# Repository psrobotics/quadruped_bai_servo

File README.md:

# Quadruped_bai_servo v1

A low cost 12DOF quadruped, actuated by hobby servos. Notice that this is an early version developed back in 2019. If you're looking for a high performance desktop quad, check out the ongoing [Quadruped bai tiny](https://github.com/psrobotics/Quadruped_bai_tiny)

This repository contains the models, BOM, electronic, simulate, as well as the source code of the project.

## Videos

[Balancing](https://www.youtube.com/watch?v=fsc0w1NeIVk)

[Walking](https://youtu.be/FCRvykWv6ok)

## Hardware

Required parts are listed below. For all printed parts, the recommended printing infill is 70%. Set up proper printing direction and support based on your printer type.

| Part Name                                                   | Quantity | Link                                                         | Info                |
| ----------------------------------------------------------- | -------- | ------------------------------------------------------------ | ------------------- |
| leg_tip                                                     | 2        | [STL file](hardware/stl)                                     | Printed part        |
| leg_tip_MIR                                                 | 2        | /                                                            | /                   |
| leg_2                                                       | 2        | /                                                            | /                   |
| leg_2_MIR                                                   | 2        | /                                                            | /                   |
| leg_link_1                                                  | 2        | /                                                            | /                   |
| leg_link_1_MIR                                              | 2        | /                                                            | /                   |
| leg_link-1                                                  | 2        | /                                                            | /                   |
| leg_link-1_MIR                                              | 2        | /                                                            | /                   |
| leg_1                                                       | 2        | /                                                            | /                   |
| leg_1_MIR                                                   | 2        | /                                                            | /                   |
| leg_1_2                                                     | 2        | /                                                            | /                   |
| leg_1_2_MIR                                                 | 2        | /                                                            | /                   |
| servo_holder_1                                              | 2        | /                                                            | /                   |
| servo_holder_1_MIR                                          | 2        | /                                                            | /                   |
| hip_joint_holder_1                                          | 2        | /                                                            | /                   |
| hip_joint_holder_1_MIR                                      | 2        | /                                                            | /                   |
| hip_holder_2                                                | 2        | /                                                            | /                   |
| hip_holder_2_MIR                                            | 2        | /                                                            | /                   |
| joint_ab_holder                                             | 2        | /                                                            | /                   |
| body_bridge                                                 | 2        | /                                                            | /                   |
| body_frame_2                                                | 1        | /                                                            | /                   |
| body_frame_1                                                | 1        | /                                                            | /                   |
| pcb_holder                                                  | 2        | /                                                            | /                   |
| M3*8                                                        | ~20      | /                                                            | Screw               |
| M3*12                                                       | ~30      | /                                                            | /                   |
| M3*16                                                       | ~20      | /                                                            | /                   |
| M2*8                                                        | ~50      | /                                                            | /                   |
| M2*15                                                       | ~50      | /                                                            | /                   |
| M2*20                                                       | ~20      | /                                                            | /                   |
| M2*26                                                       | ~20      | /                                                            | /                   |
| SF-1 0305 Self Lubricating Composite Bearing Bushing Sleeve | ~25      | [ebay](https://www.ebay.com/itm/141882850401?_trkparms=amclksrc%3DITM%26aid%3D1110006%26algo%3DHOMESPLICE.SIM%26ao%3D1%26asc%3D20200818143230%26meid%3Df2f23010710f47e39153549f7afe6b5b%26pid%3D101224%26rk%3D2%26rkt%3D5%26sd%3D141882852158%26itm%3D141882850401%26pmt%3D0%26noa%3D1%26pg%3D2047675%26algv%3DDefaultOrganicWeb%26brand%3DUnbranded&_trksid=p2047675.c101224.m-1) | For rotation joints |
| EMAX ES08A II Servo                                         | 12       | [EMAX](https://emaxmodel.com/products/emax-es08a-ii-mini-plastic-gear-analog-servo-1-8kg-sec-for-rc-models-robot) | Actuator            |

After printing your parts, insert the bearing at all 5mm holes locates around rotations joints. Then fasten  parts with M3 screws. Remember to check the rotation friction, make sure all joints can rotates freely with the servo installed. 

### Servo selection

The performance of actuators is of fundamental importance for legged robots. Even when we're building a small one. Ideal actuators for this design should be highly back-drivable, have high power density, and be torque-controllable. However, most off-the-shelf servos have nothing to do with these features. There are some high voltage brushless servos (with magnetic encoders for feedback) with relatively good performance, but they're extremely costive at this size. If you have enough budget, why not build a brushless one? Considering that you'll need 12 servos for the assembly, my suggestion is just to go for the budget choice. The EMAX ES08A (metal gear version) works fine for my build. The nylon gear version is also acceptable, but they can easily be damaged under impact.

### Body assembly

The robot consists 4 legs and a body frame. Assembly 2 legs first.

Assembly another 2 mirrored legs. Then link all legs to the body frame.

### Feet Sensor (optional)

Additional feet sensors can detect whether foot have touched the ground. This can be helpful when changing the state machine from 'swing state' to 'stance state'. The foot of Quadruped bai servo is switchable. If you decided to add feet sensors, some additional configurations are needed for the firmware (would be detailly explained later). 

Feet sensors are built around micro switches,  which detect impact from specific directions. As for the result, this design didn't work that well. A good feet sensor solution should be able to detect impacts from all directions, with low latency and clear output. [Open Dynamic Robot Initiative](https://open-dynamic-robot-initiative.github.io/) has presented an elegant solution with infrared sensor. Take that as a reference, the ongoing Quadruped bai tiny will come with better feet sensors. Assembly the feet sensor as this pic shown. (Remember to print mirrored parts for right-side legs)

Only 3 printed parts are needed to assembly the feet sensor, check [STL file](hardware/stl/feet_sensor) here.

In order to increase the friction between feet and ground, additional high-friction coating is vital. I used some glued silicone sheet on the feet tip. You can also design your feet tip and print it with high-friction material.

### Servo Calibration

Most servos have a limited motion range,  make sure the servo's motion range covers leg linkage's joint limit shown in the following pics.  Also, pre-calibrate in this step by applying an initial PWM signal to servos before installing (eg. 0°). This enables all servos to have the same PWM-joint angle mapping. You can then fine-tuning them in the firmware.

## Electronic

The controller board assembly includes servo controller, IMU, and dc-dc converter module. With an additional serial port, you can connect robot to a wireless or Bluetooth module that enables wireless control. Built around ATmega328P, the microcontroller's performance, IO is just not enough for such application. I encourage you take this schematic as a reference and switch to a high performance 32-bit microcontroller (something like STM32H7, ESP32). If you're more comfortable with AVR Arduino boards, use this design directly and it'll work.

[PCBs](electronic/) are designed with [EAGLE](https://www.autodesk.com/products/eagle/free-download). Exported Gerber file is uploaded too. If you don't want to order the PCB, you can also make it using off-the-shelf components (Arduino nano, MPU 6050, dc-dc converter, etc).

### Controller board pin assignment

Use ICSP to upload firmware and debug with the external serial port. The hardware IIC pins(A4,A5) are occupied by IMU (MPU6050 is also an 'old chip', you can replace with something like BNO080). 

### DC-DC converter

Integrated boost converter to power servos. Pre-configured output voltage is 5.5V, you can change by [replacing](https://www.ti.com/lit/ds/symlink/tps61088.pdf?ts=1644121246192#:~:text=The%20TPS61088%20is%20a%20high,size%20solution%20in%20portable%20systems.&text=The%20device%20has%2010%2DA,voltage%20up%20to%2012.6%20V.) the feedback resistor. Plug this module to the DC-DC slot on controller board.

### Battery

Single-cell lithium batteries with high current output capability(>10A) are preferred. This project uses 18650, 18350 batteries. The [battery shelf](hardware/step) can be printed and mounted under the robot frame.

## Simulate

Simplified model in [v-rep](https://www.coppeliarobotics.com/). You can use remote API to develop your simulation.

### Coordinate system in the simulation

TODO, write this docu when I'm free.

## Firmware

A simplified controller is implemented to generate trot pattern for walking. Here, I applied a state machine to easily synchronize a set of open foot trajectories (with feet sensor). The IMU unit is used to adjust body roll&pitch during the stance phase. Notice that this robot is only controlled on the kinematic level, don't expect it to resist external impacts during walking process.

## License

Under BSD-3-Clause license, COME WITH NO WARRANTIES, BUILD AT YOUR RISK.

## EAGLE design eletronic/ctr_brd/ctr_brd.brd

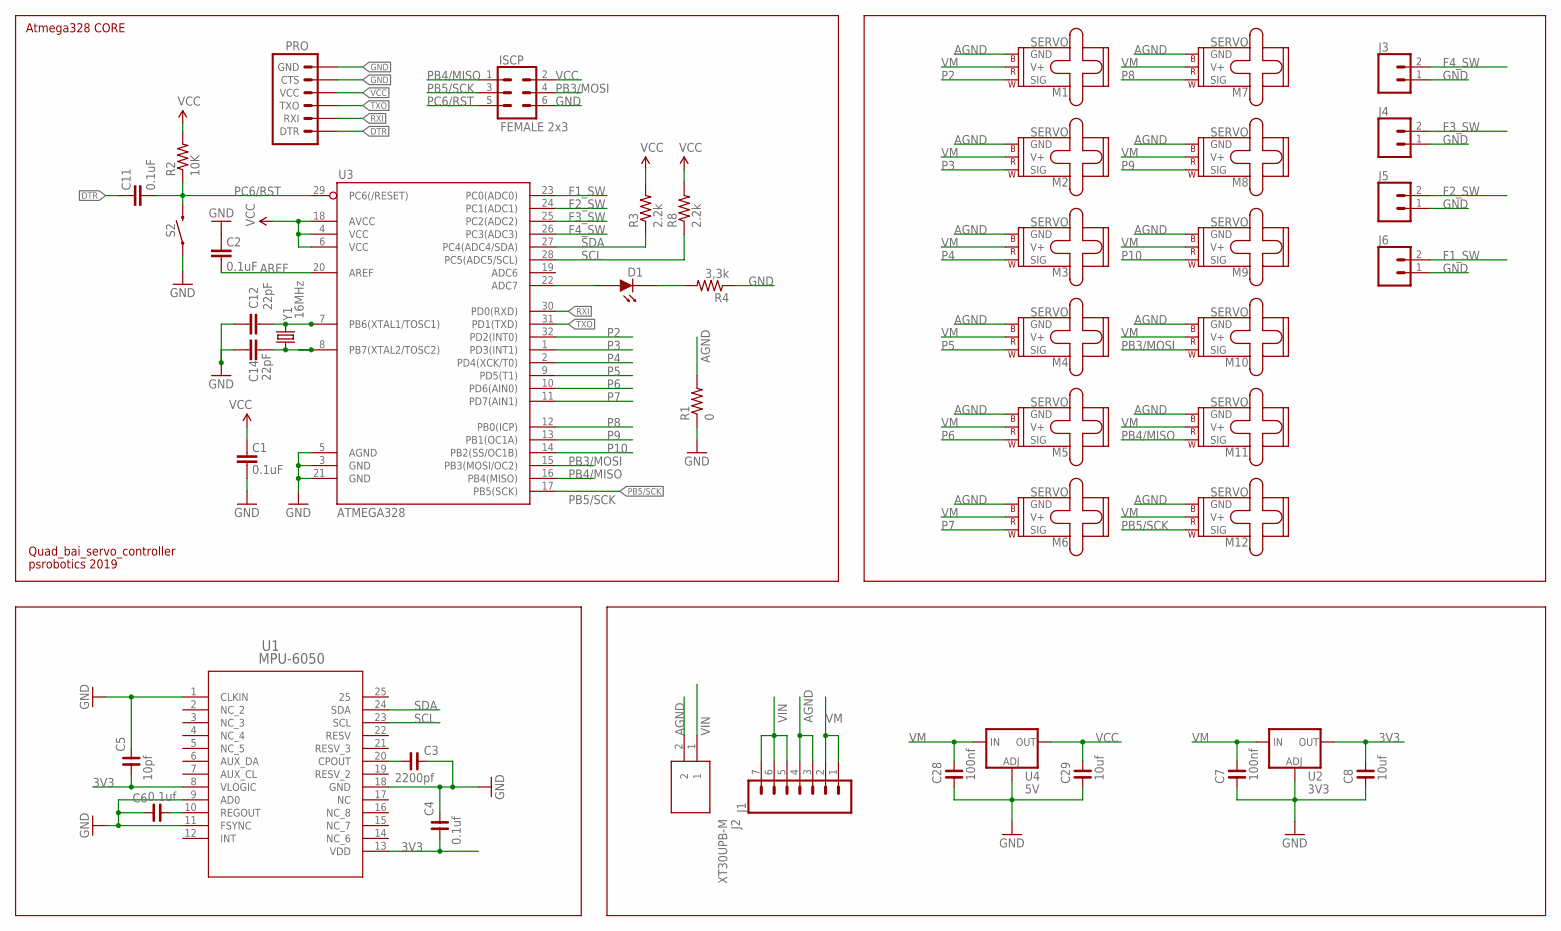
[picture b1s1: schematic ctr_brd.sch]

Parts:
C1, C2, C11: 0.1uF; 0603-CAP
C3: 2200pf; C0603
C4, C6: 0.1uf; C0603
C5: 10pf; C0603
C7, C28: 100nf; C0603
C8, C29: 10uf; C0603
C12, C14: 22pF; 0603
D1: LEDB; 0603P
ISCP: FEMALE 2x3; 2X3
J1: CONN_07LONGPADS; 1X07_LONGPADS
J2: XT30UPB-M; SHDR2W160P0X500_1X2_1020X520X1
J3, J4, J5, J6: CONN_02LOCK; 1X02_LOCK
M1, M2, M3, M4, M5, M6, M7, M8, M9, M10, M11, M12: SERVO; 1X03
PRO: FTDI Basic; 1X06
R1: 0; 0603-RES
R2: 10K; 0603-RES
R3, R8: 2.2k; 0603-RES
R4: 3,3k; 0603-RES
S2: MOMENTARY-SWITCH-SPST-SMD-6.0X3.5MM; TACTILE_SWITCH_SMD_6.0X3.5MM
U1: MPU-6050; QFN24_4X4X0P9_IVS
U2: 3V3; SOT223
U3: ATMEGA328; TQFP32-08
U4: 5V; SOT223
Y1: 16MHz; CRYSTAL-SMD-5X3.2-4PAD

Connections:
3V3: C4.1, C5.1, C8.2, U1.8 (VLOGIC), U1.13 (VDD), U2.2 (OUT), U2.4 (OUT)
AGND: J1.3, J1.4, J2.2, M1.3 (GND), M2.3 (GND), M3.3 (GND), M4.3 (GND), M5.3 (GND), M6.3 (GND), M7.3 (GND), M8.3 (GND), M9.3 (GND), M10.3 (GND), M11.3 (GND), M12.3 (GND), R1.2
AREF: C2.1, U3.20 (AREF)
DTR: C11.2, PRO.1 (DTR)
F1_SW: J6.2, U3.23 (PC0(ADC0))
F2_SW: J5.2, U3.24 (PC1(ADC1))
F3_SW: J4.2, U3.25 (PC2(ADC2))
F4_SW: J3.2, U3.26 (PC3(ADC3))
GND: C1.1, C2.2, C3.2, C4.2, C5.2, C6.2, C7.1, C8.1, C12.1, C14.1, C28.1, C29.1, ISCP.6, J3.1, J4.1, J5.1, J6.1, PRO.5 (CTS), PRO.6 (GND), R1.1, R4.1, S2.1, U1.1 (CLKIN), U1.9 (AD0), U1.11 (FSYNC), U1.18 (GND), U2.1 (ADJ), U3.3 (GND), U3.5 (AGND), U3.21 (GND), U4.1 (ADJ)
unnamed: C14.2, U3.8 (PB7(XTAL2/TOSC2)), Y1.1
unnamed: C12.2, U3.7 (PB6(XTAL1/TOSC1)), Y1.3 (2)
unnamed: C3.1, U1.20 (CPOUT)
unnamed: C6.1, U1.10 (REGOUT)
unnamed: D1.1 (D_IN), U3.22 (ADC7)
unnamed: D1.2 (D_OUT), R4.2
P2: M1.1 (SIG), U3.32 (PD2(INT0))
P3: M2.1 (SIG), U3.1 (PD3(INT1))
P4: M3.1 (SIG), U3.2 (PD4(XCK/T0))
P5: M4.1 (SIG), U3.9 (PD5(T1))
P6: M5.1 (SIG), U3.10 (PD6(AIN0))
P7: M6.1 (SIG), U3.11 (PD7(AIN1))
P8: M7.1 (SIG), U3.12 (PB0(ICP))
P9: M8.1 (SIG), U3.13 (PB1(OC1A))
P10: M9.1 (SIG), U3.14 (PB2(SS/OC1B))
PB3/MOSI: ISCP.4, M10.1 (SIG), U3.15 (PB3(MOSI/OC2))
PB4/MISO: ISCP.1, M11.1 (SIG), U3.16 (PB4(MISO))
PB5/SCK: ISCP.3, M12.1 (SIG), U3.17 (PB5(SCK))
PC6/RST: C11.1, ISCP.5, R2.1, S2.2, U3.29 (PC6(/RESET))
RXI: PRO.2 (RXI), U3.30 (PD0(RXD))
SCL: R8.1, U1.23 (SCL), U3.28 (PC5(ADC5/SCL))
SDA: R3.1, U1.24 (SDA), U3.27 (PC4(ADC4/SDA))
TXO: PRO.3 (TXO), U3.31 (PD1(TXD))
VCC: C1.2, C29.2, ISCP.2, PRO.4 (VCC), R2.2, R3.2, R8.2, U3.4 (VCC), U3.6 (VCC), U3.18 (AVCC), U4.2 (OUT), U4.4 (OUT)
VIN: J1.5, J1.6, J1.7, J2.1
VM: C7.2, C28.2, J1.1, J1.2, M1.2 (V+), M2.2 (V+), M3.2 (V+), M4.2 (V+), M5.2 (V+), M6.2 (V+), M7.2 (V+), M8.2 (V+), M9.2 (V+), M10.2 (V+), M11.2 (V+), M12.2 (V+), U2.3 (IN), U4.3 (IN)

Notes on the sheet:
Atmega328 CORE
Quad_bai_servo_controller
psrobotics 2019

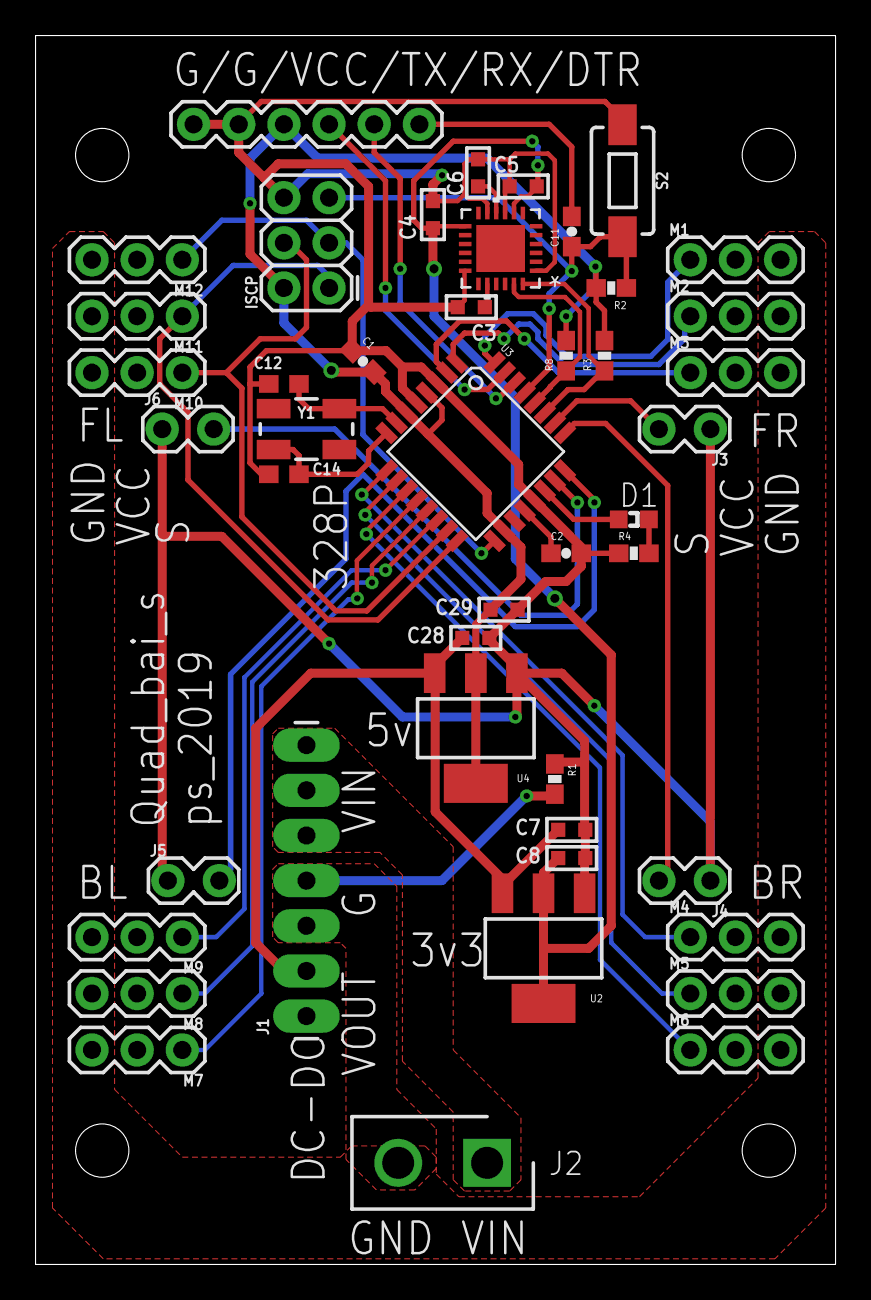
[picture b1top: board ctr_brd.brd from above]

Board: 2 copper layers, 45.0 x 69.1 mm, 45 parts (0 on the bottom side), 35 nets.

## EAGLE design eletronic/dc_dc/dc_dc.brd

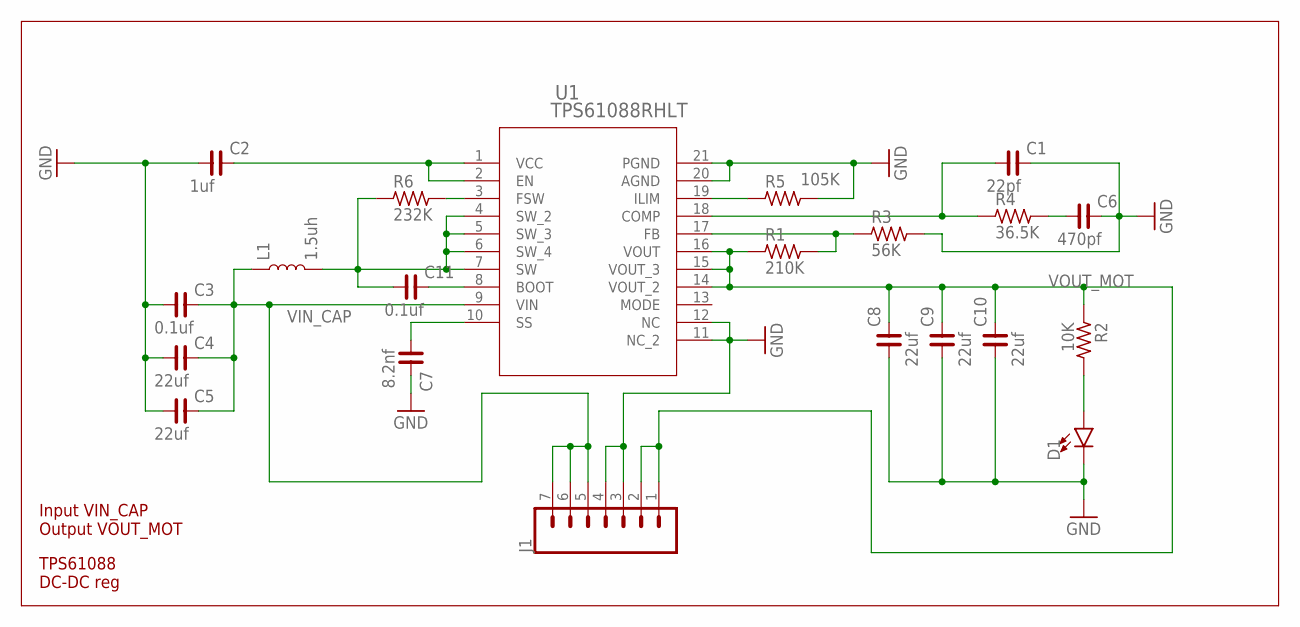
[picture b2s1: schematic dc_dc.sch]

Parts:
C1: 22pf; C0603
C2: 1uf; C0603
C3, C11: 0.1uf; C0603
C4, C5, C8, C9, C10: 22uf; C1210
C6: 470pf; C0603
C7: 8.2nf; C0603
D1: LED0603; LED-0603
J1: CONN_07LONGPADS; 1X07_LONGPADS
L1: 1.5uh; CR75
R1: 210K; R0603
R2: 10K; R0603
R3: 56K; R0603
R4: 36.5K; R0603
R5: 105K; R0603
R6: 232K; R0603
U1: TPS61088RHLT; RHL0020A_TEX

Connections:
GND: C1.2, C2.1, C3.1, C4.1, C5.1, C6.2, C7.2, C8.1, C9.1, C10.1, D1.C, J1.3, J1.4, R3.2, R5.2, U1.11 (NC_2), U1.12 (NC), U1.20 (AGND), U1.21 (PGND)
unnamed: C7.1, U1.10 (SS)
unnamed: R5.1, U1.19 (ILIM)
unnamed: C1.1, R4.1, U1.18 (COMP)
unnamed: C6.1, R4.2
unnamed: C2.2, U1.1 (VCC), U1.2 (EN)
unnamed: R1.2, R3.1, U1.17 (FB)
unnamed: D1.A, R2.2
unnamed: C11.2, U1.8 (BOOT)
unnamed: C11.1, L1.P$2 (2), R6.1, U1.4 (SW_2), U1.5 (SW_3), U1.6 (SW_4), U1.7 (SW)
unnamed: R6.2, U1.3 (FSW)
VIN_CAP: C3.2, C4.2, C5.2, J1.5, J1.6, J1.7, L1.P$1 (1), U1.9 (VIN)
VOUT_MOT: C8.2, C9.2, C10.2, J1.1, J1.2, R1.1, R2.1, U1.14 (VOUT_2), U1.15 (VOUT_3), U1.16 (VOUT)

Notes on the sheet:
TPS61088 DC-DC reg
Input VIN_CAP Output VOUT_MOT

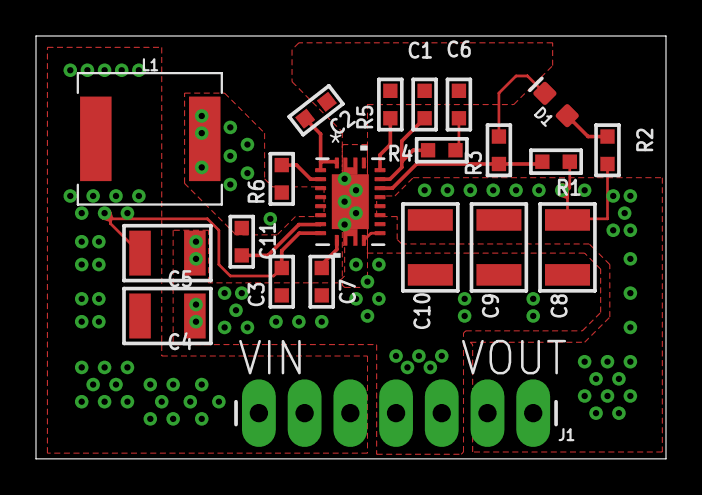
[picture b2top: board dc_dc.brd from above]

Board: 2 copper layers, 35.0 x 23.5 mm, 21 parts (0 on the bottom side), 13 nets.

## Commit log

2022-01-19 add: 22_0120 guide
2022-01-19 fix: 0120
2022-01-20 Create LICENSE
2022-02-02 add: 0203
2022-02-03 add: 0204-2
2022-02-06 add: 0206 feet sensor
2022-02-06 add: 0206 servo cali
2022-02-06 add: 0206 fix1
2022-02-06 add: 0206 sim
2022-02-06 add: 0207 firmware
2022-02-06 add: 0207 lic
2022-02-07 fix: 0207 broken link

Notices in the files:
parts and their libraries:
SparkFun-Capacitors: Licensing: Creative Commons ShareAlike 4.0 International - https://creativecommons.org/licenses/by-sa/4.0
rc-master-smd: Copyright (C) 2007, Bob Starr
m-pad-2.1: License : GNU General Public License version 2 (see bottom)
